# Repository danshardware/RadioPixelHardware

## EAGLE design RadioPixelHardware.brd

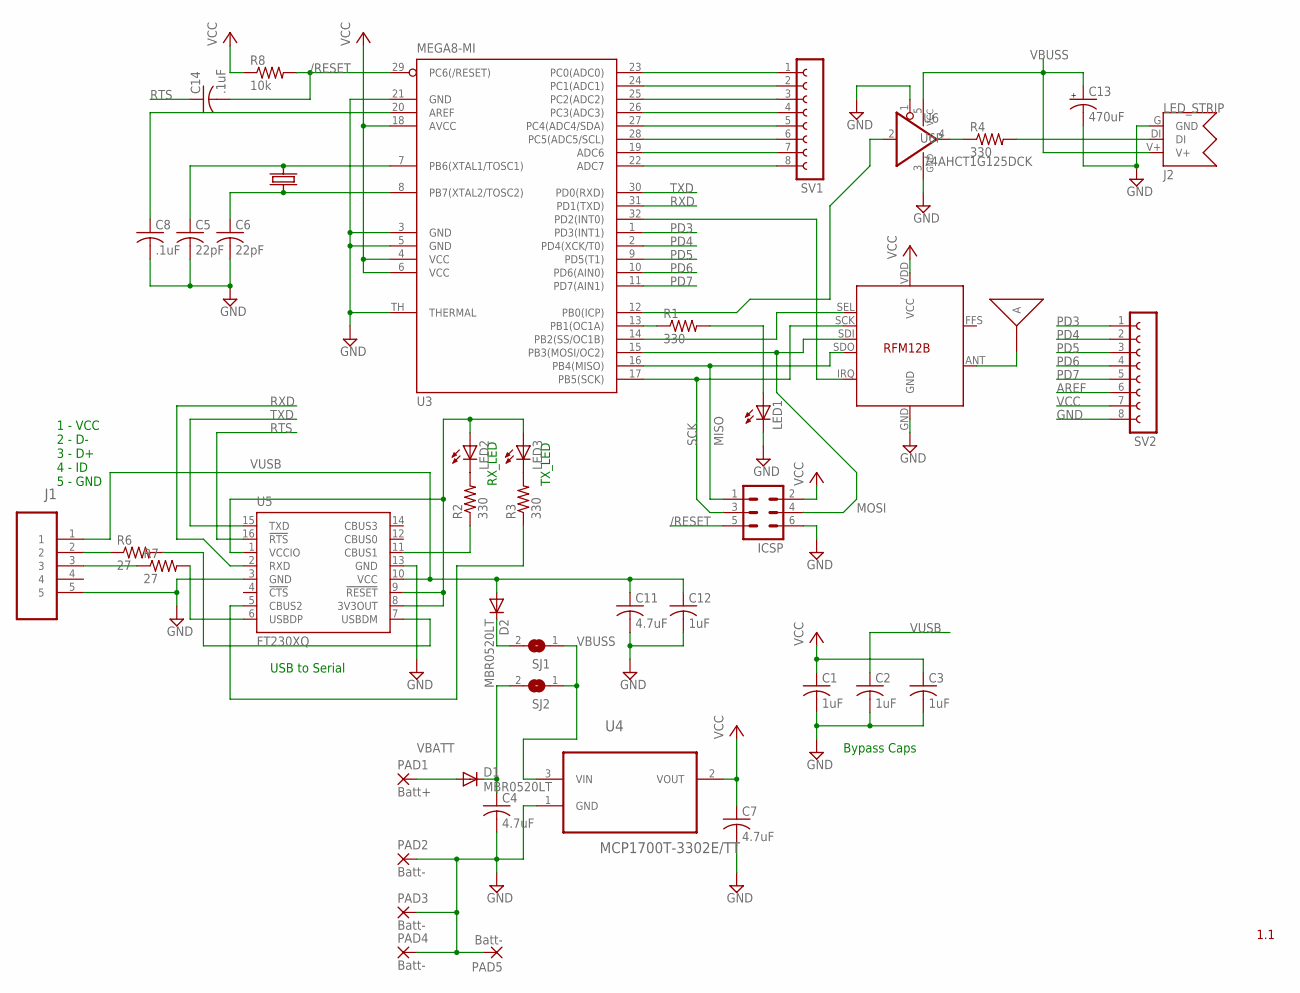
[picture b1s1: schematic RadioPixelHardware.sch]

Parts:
C1, C2, C3, C12: 1uF; C0603
C4, C7, C11: 4.7uF; C0603
C5, C6: 22pF; C0603
C8, C14: .1uF; C0603
C13: 470uF; TT2D4L
D1, D2: MBR0520LT; SOD123
ICSP: MA03-2
J1: 47346-0001; MOLEX_47346-0001
J2: LED_STRIP; LEDSTRIP_HEAD
LED1, LED2, LED3: LEDSML0603; SML0603
PAD1: Batt+; 1,6/0,8
PAD2, PAD3, PAD4, PAD5: Batt-; 1,6/0,8
R1, R2, R3, R4: 330; R0603
R6, R7: 27; R0603
R8: 10k; R0603
SJ1, SJ2: SJ
SV1, SV2: FE08-1; FE08
U2: RFM12B
U3: MEGA8-MI; MLF32-TH
U4: MCP1700T-3302E/TT; SOT95P237X112-3N
U5: FT230XQ; QFN16
U6: 74AHCT1G125DCK; SC70-5
U$2: ANTANT-PCB-868MHZ; ANT-900MHZ-60DBM
X1: CRYSTAL3.2MMX2.5MM; XTAL-SMD-3.2X2.5

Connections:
/RESET: C14.2, ICSP.5, R8.2, U3.29 (PC6(/RESET))
AREF: C8.1, SV2.6, U3.20 (AREF)
GND: C1.2, C2.2, C3.2, C4.2, C5.2, C6.2, C7.2, C8.2, C11.2, C12.2, C13.-, ICSP.6, J1.5, J2.G (GND), LED1.C, PAD2.1, PAD3.1, PAD4.1, PAD5.1, SV2.8, U2.GND, U3.3 (GND), U3.5 (GND), U3.21 (GND), U3.TH (THERMAL), U4.1 (GND), U5.3 (GND), U5.13 (GND), U6.1 (OE), U6.3 (GND)
MISO: ICSP.1, U2.SDO, U3.16 (PB4(MISO))
MOSI: ICSP.4, U2.SDI, U3.15 (PB3(MOSI/OC2))
unnamed: U2.SEL, U3.14 (PB2(SS/OC1B))
unnamed: U2.IRQ, U3.32 (PD2(INT0))
unnamed: U2.ANT, U$2.P$1
unnamed: R1.1, U3.13 (PB1(OC1A))
unnamed: LED1.A, R1.2
unnamed: R4.1, U6.4 (O)
unnamed: R2.1, U5.11 (CBUS1)
unnamed: U3.12 (PB0(ICP)), U6.2 (I)
unnamed: R7.2, U5.6 (USBDP)
unnamed: R6.2, U5.7 (USBDM)
unnamed: C4.1, D1.C, SJ2.2
unnamed: LED2.C, R2.2
unnamed: LED3.C, R3.2
unnamed: J1.2, R6.1
unnamed: R3.1, U5.5 (CBUS2)
unnamed: C5.1, U3.7 (PB6(XTAL1/TOSC1)), X1.3 (2)
unnamed: D2.C, SJ1.2
unnamed: C6.1, U3.8 (PB7(XTAL2/TOSC2)), X1.1
unnamed: J1.3, R7.1
unnamed: SV1.1, U3.23 (PC0(ADC0))
unnamed: SV1.2, U3.24 (PC1(ADC1))
unnamed: SV1.3, U3.25 (PC2(ADC2))
unnamed: SV1.4, U3.26 (PC3(ADC3))
unnamed: SV1.5, U3.27 (PC4(ADC4/SDA))
unnamed: SV1.6, U3.28 (PC5(ADC5/SCL))
unnamed: SV1.7, U3.19 (ADC6)
unnamed: SV1.8, U3.22 (ADC7)
unnamed: J2.DI, R4.2
PD3: SV2.1, U3.1 (PD3(INT1))
PD4: SV2.2, U3.2 (PD4(XCK/T0))
PD5: SV2.3, U3.9 (PD5(T1))
PD6: SV2.4, U3.10 (PD6(AIN0))
PD7: SV2.5, U3.11 (PD7(AIN1))
RTS: C14.1, U5.16 (!RTS)
RXD: U3.31 (PD1(TXD)), U5.2 (RXD)
SCK: ICSP.3, U2.SCK, U3.17 (PB5(SCK))
TXD: U3.30 (PD0(RXD)), U5.15 (TXD)
USB3V3: LED2.A, LED3.A, U5.1 (VCCIO), U5.8 (3V3OUT), U5.9 (!RESET)
VBATT: D1.A, PAD1.1
VBUSS: C13.+, J2.V+, SJ1.1, SJ2.1, U4.3 (VIN), U6.5 (VCC)
VCC: C1.1, C3.1, C7.1, ICSP.2, R8.1, SV2.7, U2.VDD (VCC), U3.4 (VCC), U3.6 (VCC), U3.18 (AVCC), U4.2 (VOUT)
VUSB: C2.1, C11.1, C12.1, D2.A, J1.1, U5.10 (VCC)

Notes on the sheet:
Bypass Caps
1 - VCC 2 - D- 3 - D+ 4 - ID 5 - GND
USB to Serial
RX_LED
TX_LED
1.1

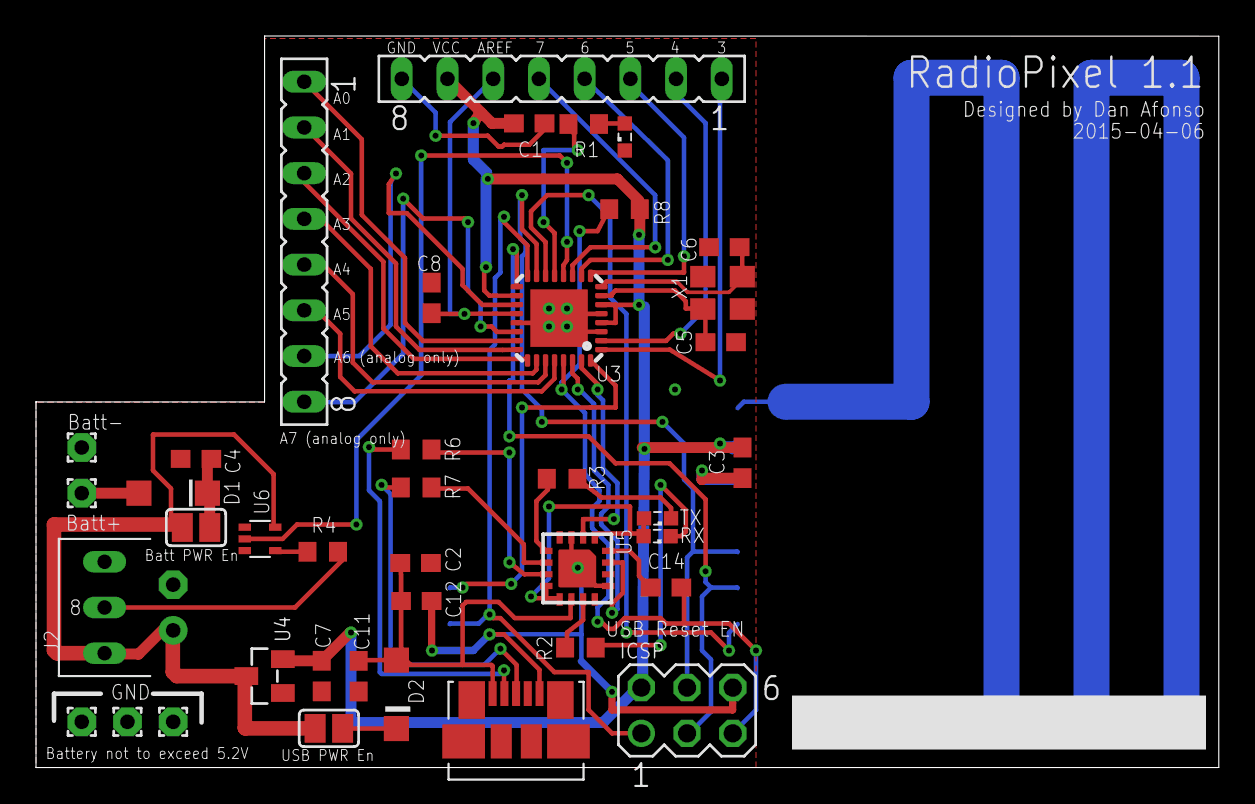
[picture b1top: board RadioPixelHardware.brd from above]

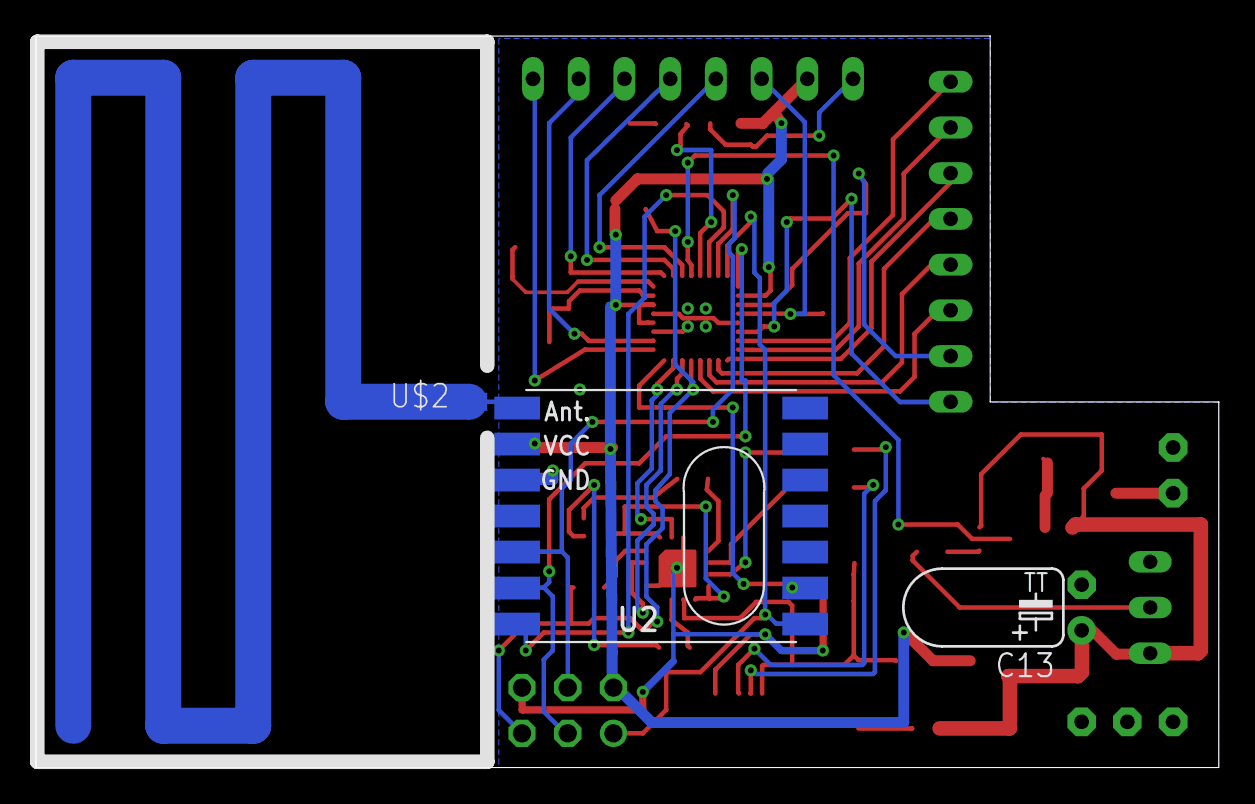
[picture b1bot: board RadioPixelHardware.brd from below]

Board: 2 copper layers, 65.7 x 40.6 mm, 43 parts (3 on the bottom side), 47 nets.

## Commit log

2015-11-22 :circus_tent: Added .gitattributes & .gitignore files
2015-11-22 Radio Pixel Board
    Contains files that comprise the RadioPixel master hardware and assembly
    instructions
